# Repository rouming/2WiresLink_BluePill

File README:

This is DC low voltage (up to 60v) PLC modem based on the following
schematics https://www.radiolocman.com/shem/schematics.html?di=148255
with only one modification for small 500k carrier frequency: C3 was
changed from 100pF to 1nF.

Firmware is written for STM32F103 BluePill board.  Modem PCB is designed
in such a way that BluePill can be directly pluged in using hardware
USART1 support.

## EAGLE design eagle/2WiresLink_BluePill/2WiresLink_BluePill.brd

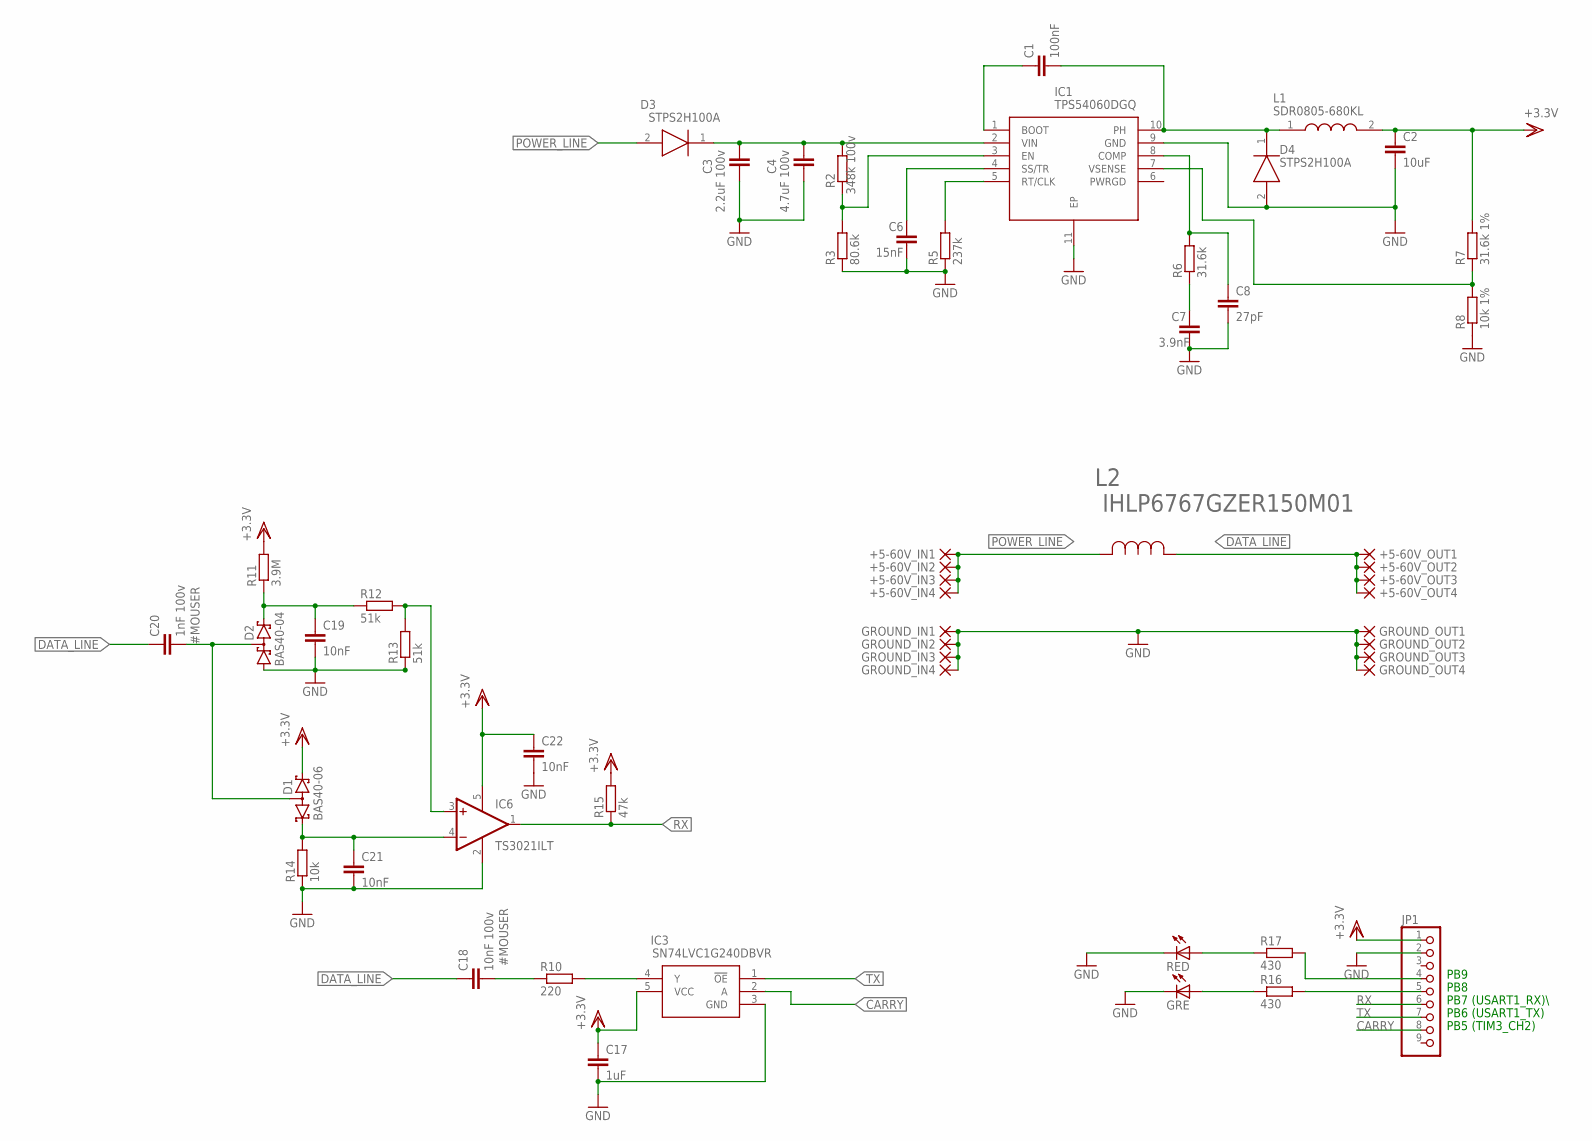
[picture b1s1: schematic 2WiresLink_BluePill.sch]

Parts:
+5-60V_IN1, +5-60V_IN2, +5-60V_IN3, +5-60V_IN4, +5-60V_OUT1, +5-60V_OUT2, +5-60V_OUT3, +5-60V_OUT4: PAD-0820-S; 0820-S
C1: 100nF; C0603; MPN C0603C104K5RECAUTO
C2: 10uF; C0603; MPN GRM188R61A106KE69D
C3: 2.2uF 100v; C1210; MPN C3225X7R2A225K230AB
C4: 4.7uF 100v; C1210; MPN CGA6M3X7S2A475K200AB
C6: 15nF; C0603; MPN C0603C153K5RACTU
C7: 3.9nF; C0603; MPN GCM1885C1H392JA16D
C8: 27pF; C0603; MPN 06035A270JAT2A
C17: 1uF; C0603; MPN 0603YD105KAT2A
C18: 10nF 100v; C0603; MPN GCM188R72A103KA37D
C19, C22: 10nF; C0603; MPN C0603C103K5RACAUTO7411
C20: 1nF 100v; C0603; MPN 06031C102KAT2A
C21: 10nF; C0603
D1: BAS40-06; SOT23; MPN BAS40-06-E3-08
D2: BAS40-04; SOT23; MPN BAS40-04-7-F
D3, D4: STPS2H100A; DIOM5126X265N; MPN STPS2H100A
GRE: GRE; CHIP-LED0805; MPN SML-LXT0805GW-TR
GROUND_IN1, GROUND_IN2, GROUND_IN3, GROUND_IN4: PAD-0820-S; 0820-S
GROUND_OUT1, GROUND_OUT2, GROUND_OUT3, GROUND_OUT4: PAD-0820-S; 0820-S
IC1: TPS54060DGQ; SOP50P490X110-11N; MPN TPS54060DGQR
IC3: SN74LVC1G240DBVR; SOT95P280X145-5N; MPN SN74LVC1G240DBVR
IC6: TS3021ILT; SOT95P280X145-5N; MPN TS3021ILT
JP1: PINHD-1X9; 1X09-BIG
L1: SDR0805-680KL; MPN SDR0805-680KL
L2: IHLP6767GZER150M01; IND_IHLP-6767GZ; MPN IHLP6767GZER150M01
R2: 348k 100v; R0603; MPN RG1608P-3483-D-T5
R3: 80.6k; R0603; MPN CRCW060380K6FKEA
R5: 237k; R0603; MPN AC0603FR-07237KL
R6: 31.6k; R0603; MPN AC0603FR-0731K6L
R7: 31.6k 1%; R0603; MPN AC0603FR-0731K6L
R8: 10k 1%; R0603; MPN CRCW060310K0FKEAC
R10: 220; R0603; MPN RC0603FR-07220RL
R11: 3.9M; R0603; MPN RC0603FR-073M9L
R12, R13: 51k; R0603; MPN RC0603FR-0751KL
R14: 10k; R0603; MPN CRCW060310K0FKEAC
R15: 47k; R0603; MPN RC0603FR-0747KL
R16, R17: 430; R0603; MPN RC0603FR-07430RL
RED: RED; CHIP-LED0805; MPN SML-LXT0805IW-TR

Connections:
CARRY: IC3.2 (A), JP1.8
DATA_LINE: +5-60V_OUT1.P$1, +5-60V_OUT2.P$1, +5-60V_OUT3.P$1, +5-60V_OUT4.P$1, C18.1, C20.1, L2.1
GND: C2.2, C3.2, C4.2, C6.2, C7.2, C8.2, C17.2, C19.2, C21.2, C22.2, D2.1 (A1), D4.2 (A), GRE.C, GROUND_IN1.P$1, GROUND_IN2.P$1, GROUND_IN3.P$1, GROUND_IN4.P$1, GROUND_OUT1.P$1, GROUND_OUT2.P$1, GROUND_OUT3.P$1, GROUND_OUT4.P$1, IC1.9 (GND), IC1.11 (EP), IC3.3 (GND), IC6.2 (V-), JP1.2, R3.1, R5.1, R8.1, R13.1, R14.1, RED.C
unnamed: C1.2, D4.1 (K), IC1.10 (PH), L1.1
unnamed: C1.1, IC1.1 (BOOT)
unnamed: C7.1, R6.1
unnamed: C8.1, IC1.8 (COMP), R6.2
unnamed: IC1.3 (EN), R2.1, R3.2
unnamed: IC1.7 (VSENSE), R7.1, R8.2
unnamed: C3.1, C4.1, D3.1 (K), IC1.2 (VIN), R2.2
unnamed: C6.1, IC1.4 (SS/TR)
unnamed: IC1.5 (RT/CLK), R5.2
unnamed: JP1.4, R17.2
unnamed: JP1.5, R16.2
unnamed: IC3.4 (Y), R10.2
unnamed: C18.2, R10.1
unnamed: C19.1, D2.2 (C2), R11.1, R12.1
unnamed: IC6.3 (+IN), R12.2, R13.2
unnamed: C20.2, D1.3 (AA), D2.3 (C1A2)
unnamed: C21.1, D1.1 (K1), IC6.4 (-IN), R14.2
unnamed: GRE.A, R16.1
unnamed: R17.1, RED.A
POWER_LINE: +5-60V_IN1.P$1, +5-60V_IN2.P$1, +5-60V_IN3.P$1, +5-60V_IN4.P$1, D3.2 (A), L2.2
RX: IC6.1 (OUT), JP1.6, R15.1
TX: IC3.1 (!OE), JP1.7
VDD: C2.1, C17.1, C22.1, D1.2 (K2), IC3.5 (VCC), IC6.5 (V+), JP1.1, L1.2, R7.2, R11.2, R15.2

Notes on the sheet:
PB7 (USART1_RX)\
PB6 (USART1_TX)
PB5 (TIM3_CH2)
PB9
PB8

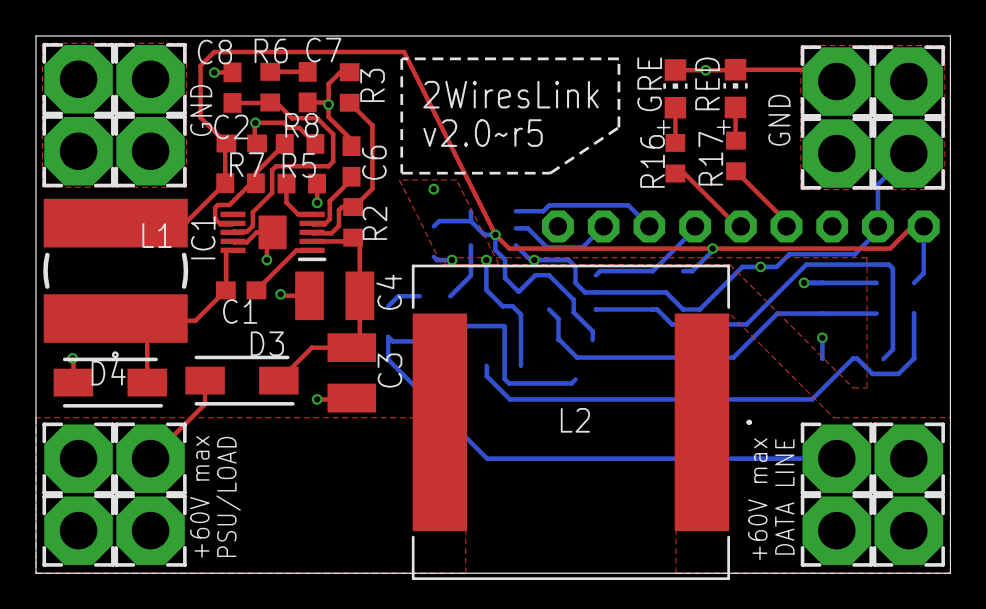
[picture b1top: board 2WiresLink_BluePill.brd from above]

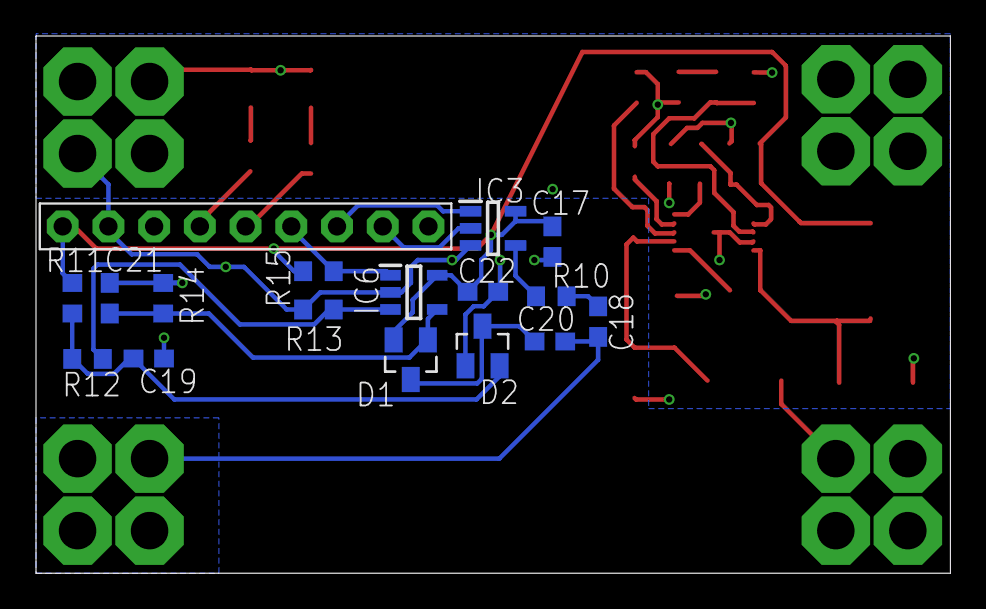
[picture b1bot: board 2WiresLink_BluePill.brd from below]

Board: 2 copper layers, 50.8 x 29.8 mm, 55 parts (17 on the bottom side), 26 nets.

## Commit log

2019-10-06 Initial commit.
2019-10-06 firmware: decrease carry frequency and baud rate
    Decrease carry frequency from 500k to 100k and
    baud rate from 19200 to 4800 in order to increase
    cable length and packet delivery under high load.
2019-10-06 eagle: increase C21 capacity from 1nF to 10nF
    In previous commit carry frequency and baud rate was decreased,
    C21 capacity should be increased.

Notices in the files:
parts and their libraries:
dpads: Copyright (C) 2004, Bob Starr (bobstarr@mindspring.com)
